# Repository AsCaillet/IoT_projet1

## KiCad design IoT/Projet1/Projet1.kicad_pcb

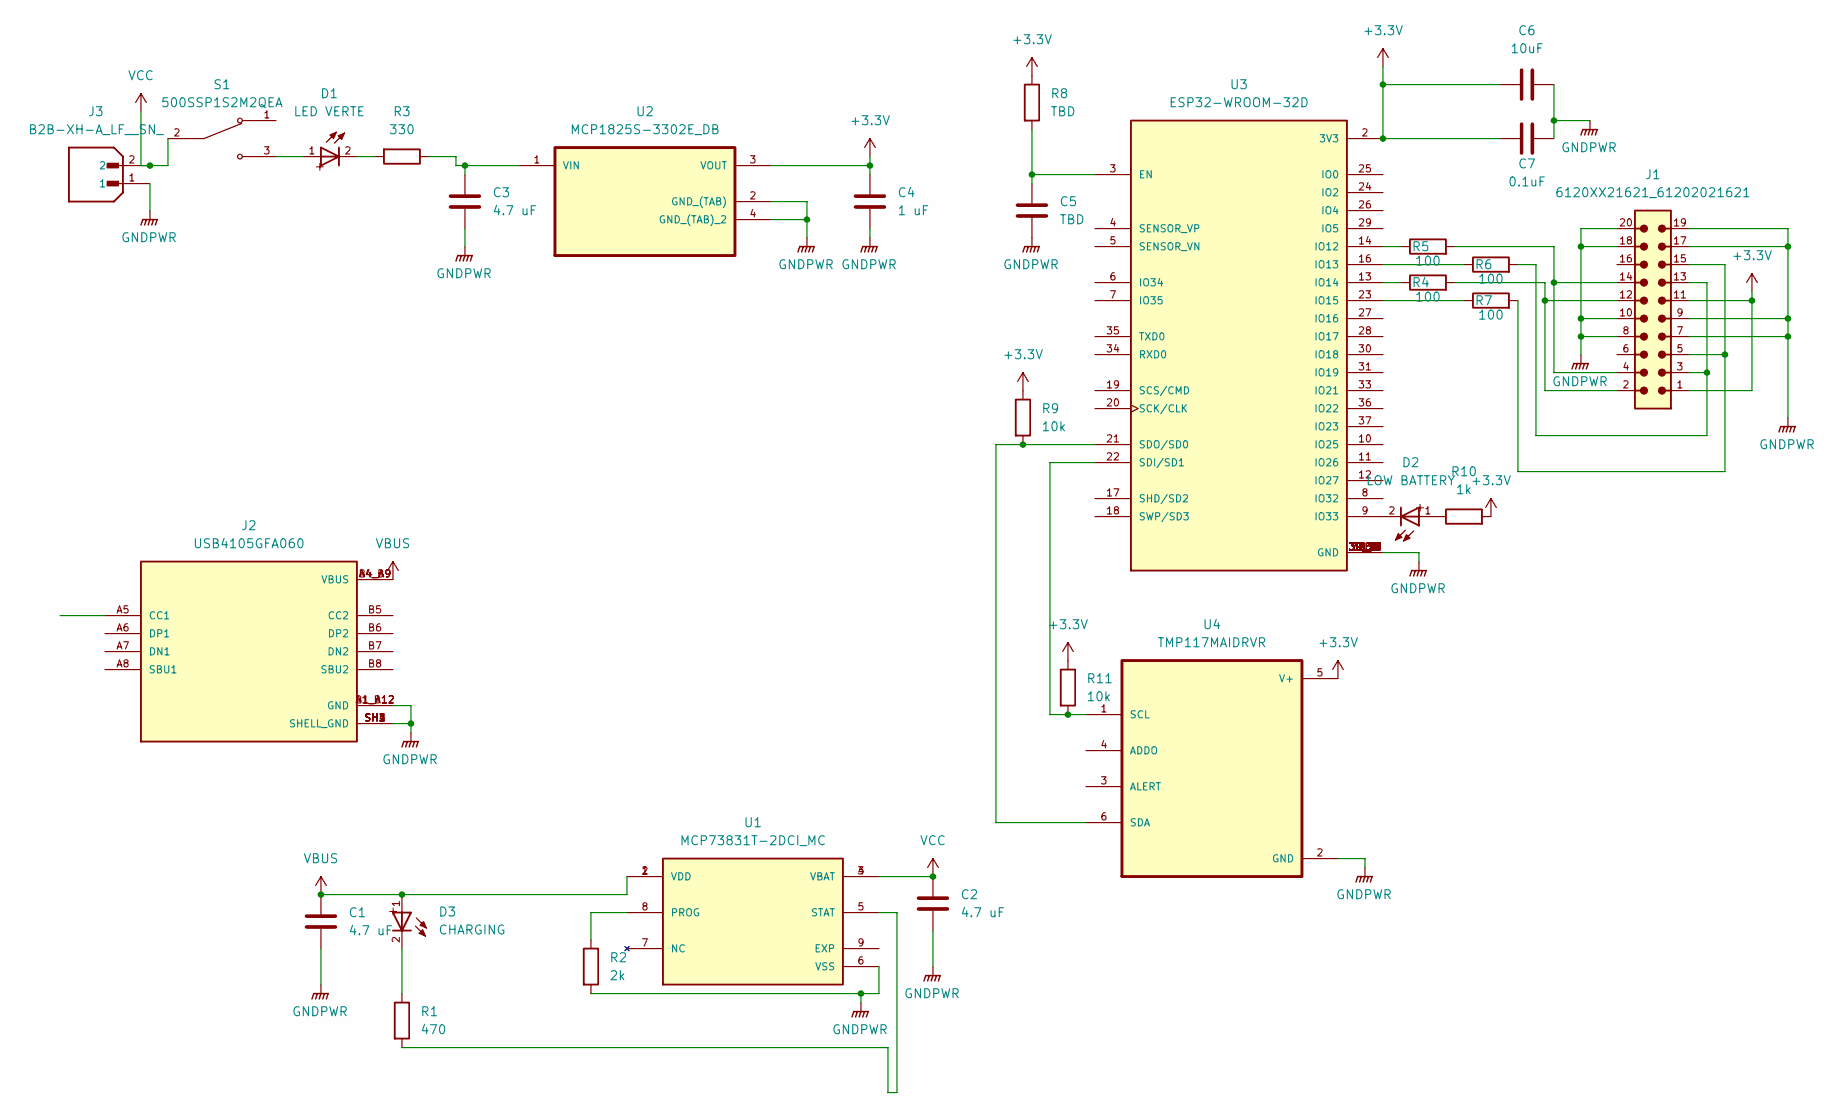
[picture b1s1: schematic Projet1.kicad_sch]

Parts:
C1, C2, C3: 4.7 uF; C_0805_2012Metric
C4: 1 uF; C_0805_2012Metric
C5: TBD; C_0805_2012Metric
C6: 10uF; C_0805_2012Metric
C7: 0.1uF; C_0805_2012Metric
D1: LED VERTE; LED_0805_2012Metric
D2: LOW BATTERY; LED_0805_2012Metric
D3: CHARGING; LED_0805_2012Metric
J1: 6120XX21621_61202021621; 61202021621; PART-NUMBER 61202021621
J2: USB4105GFA060; GCT_USB4105GFA060; PARTREV B3
J3: B2B-XH-A_LF__SN_; JST_B2B-XH-A_LF__SN_; PARTREV N/A
R1: 470; R_0805_2012Metric
R2: 2k; R_0805_2012Metric
R3: 330; R_0805_2012Metric
R4, R5, R6, R7: 100; R_0805_2012Metric
R8: TBD; R_0805_2012Metric
R9, R11: 10k; R_0805_2012Metric
R10: 1k; R_0805_2012Metric
S1: 500SSP1S2M2QEA; SW_500SSP1S2M2QEA; PARTREV C
U1: MCP73831T-2DCI_MC; SON50P200X300X100-9N; PARTREV H; DigiKey_Part_Number MCP73831T-2DCI/MCTR-ND
U2: MCP1825S-3302E_DB; SOT230P700X180-4N
U3: ESP32-WROOM-32D; MODULE_ESP32-WROOM-32D; PARTREV 1.9
U4: TMP117MAIDRVR; SON65P200X200X80-7N

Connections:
+3.3V: C4.1, C6.1, C7.1, J1.1, J1.11, R8.1, R9.1, R10.2, R11.1, U2.3 (VOUT), U3.2 (3V3), U4.5 (V+)
GNDPWR: C1.2, C2.2, C3.2, C4.2, C5.2, C6.2, C7.2, J1.7, J1.8, J1.9, J1.10, J1.17, J1.18, J1.19, J1.20, J2.A1_B12 (GND), J2.B1_A12 (GND), J2.SH1 (SHELL_GND), J2.SH2 (SHELL_GND), J2.SH3 (SHELL_GND), J2.SH4 (SHELL_GND), J3.1, R2.2, U1.6 (VSS), U2.2 (GND_(TAB)), U2.4 (GND_(TAB)_2), U3.1 (GND), U3.15 (GND), U3.38 (GND), U3.39_1 (GND), U3.39_2 (GND), U3.39_3 (GND), U3.39_4 (GND), U3.39_5 (GND), U3.39_6 (GND), U3.39_7 (GND), U3.39_8 (GND), U3.39_9 (GND), U3.39_10 (GND), U3.39_11 (GND), U3.39_12 (GND), U3.39_13 (GND), U3.39_14 (GND), U3.39_15 (GND), U3.39_16 (GND), U3.39_17 (GND), U3.39_18 (GND), U3.39_19 (GND), U3.39_20 (GND), U3.39_21 (GND), U4.2 (GND)
unnamed: D1.1, S1.3
unnamed: D1.2, R3.2
unnamed: D2.1, R10.1
unnamed: D3.2, R1.1
unnamed: J1.2, J1.12, R4.2
unnamed: J1.3, J1.13, R6.2
unnamed: J1.4, J1.14, R5.2
unnamed: J1.5, J1.15, R7.2
unnamed: R2.1, U1.8 (PROG)
unnamed: R1.2, U1.5 (STAT)
unnamed: C3.1, R3.1, U2.1 (VIN)
unnamed: C5.1, R8.2, U3.3 (EN)
unnamed: R5.1, U3.14 (IO12)
unnamed: R6.1, U3.16 (IO13)
unnamed: R4.1, U3.13 (IO14)
unnamed: R7.1, U3.23 (IO15)
unnamed: D2.2, U3.9 (IO33)
unnamed: R11.2, U3.22 (SDI/SD1), U4.1 (SCL)
unnamed: R9.2, U3.21 (SDO/SD0), U4.6 (SDA)
VBUS: C1.1, D3.1, J2.A4_B9 (VBUS), J2.B4_A9 (VBUS), U1.1 (VDD), U1.2 (VDD)
VCC: C2.1, J3.2, S1.2, U1.3 (VBAT), U1.4 (VBAT)

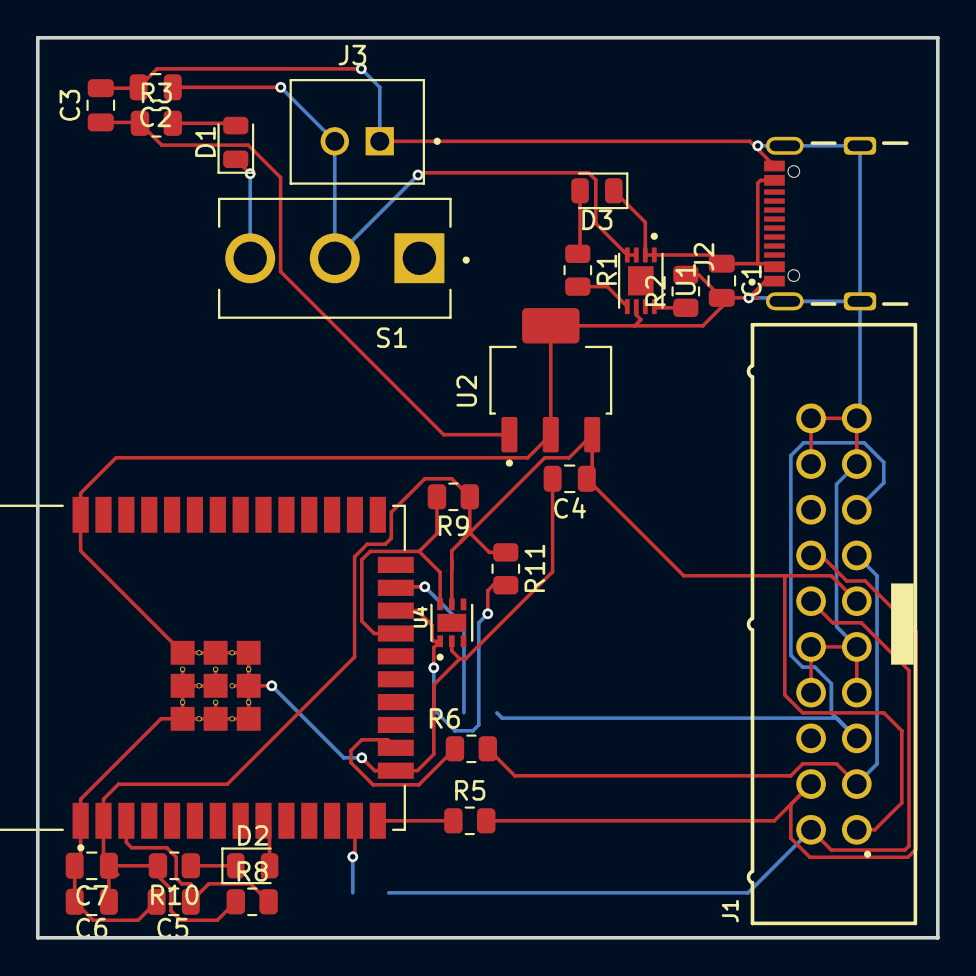
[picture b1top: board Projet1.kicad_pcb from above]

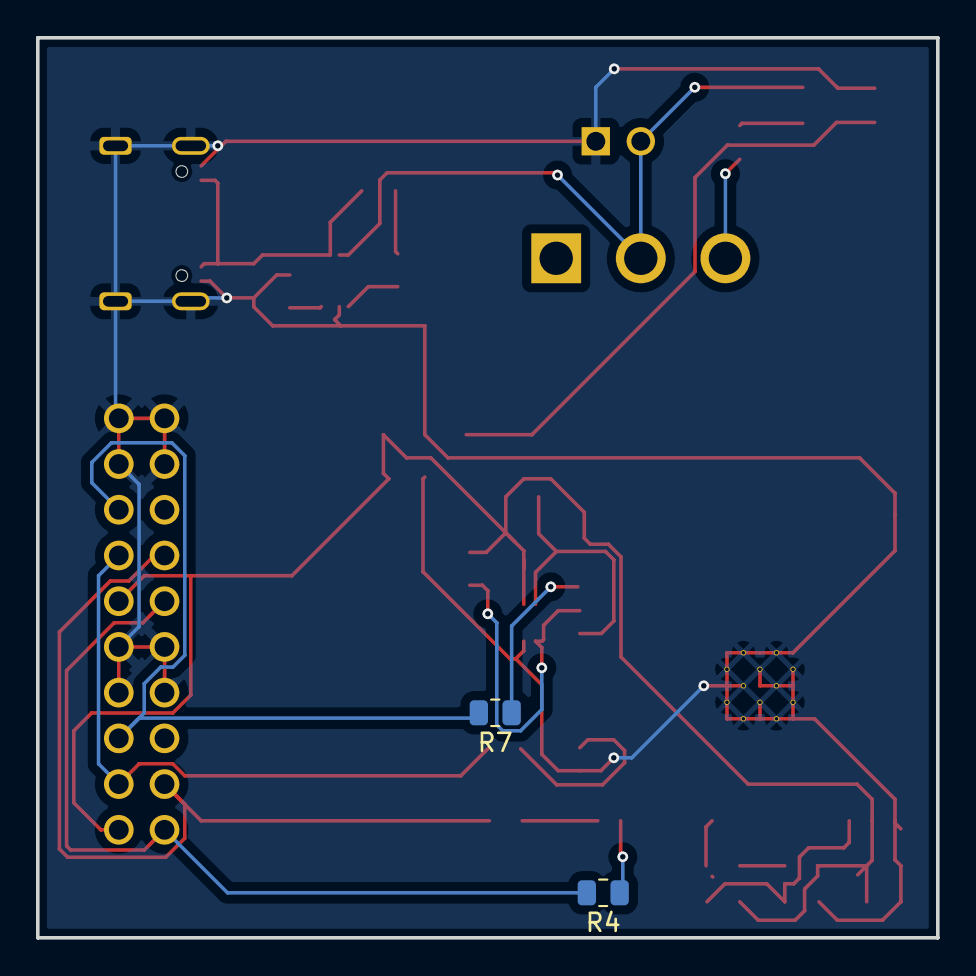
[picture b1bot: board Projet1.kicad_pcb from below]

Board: 2 copper layers, 50.0 x 50.0 mm, 29 parts (2 on the bottom side), 23 nets.

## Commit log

2024-10-24 Ajout des fichiers KiCad
2024-10-24 Ajout R_up I2C
2024-10-24 Ajout plan de masse
